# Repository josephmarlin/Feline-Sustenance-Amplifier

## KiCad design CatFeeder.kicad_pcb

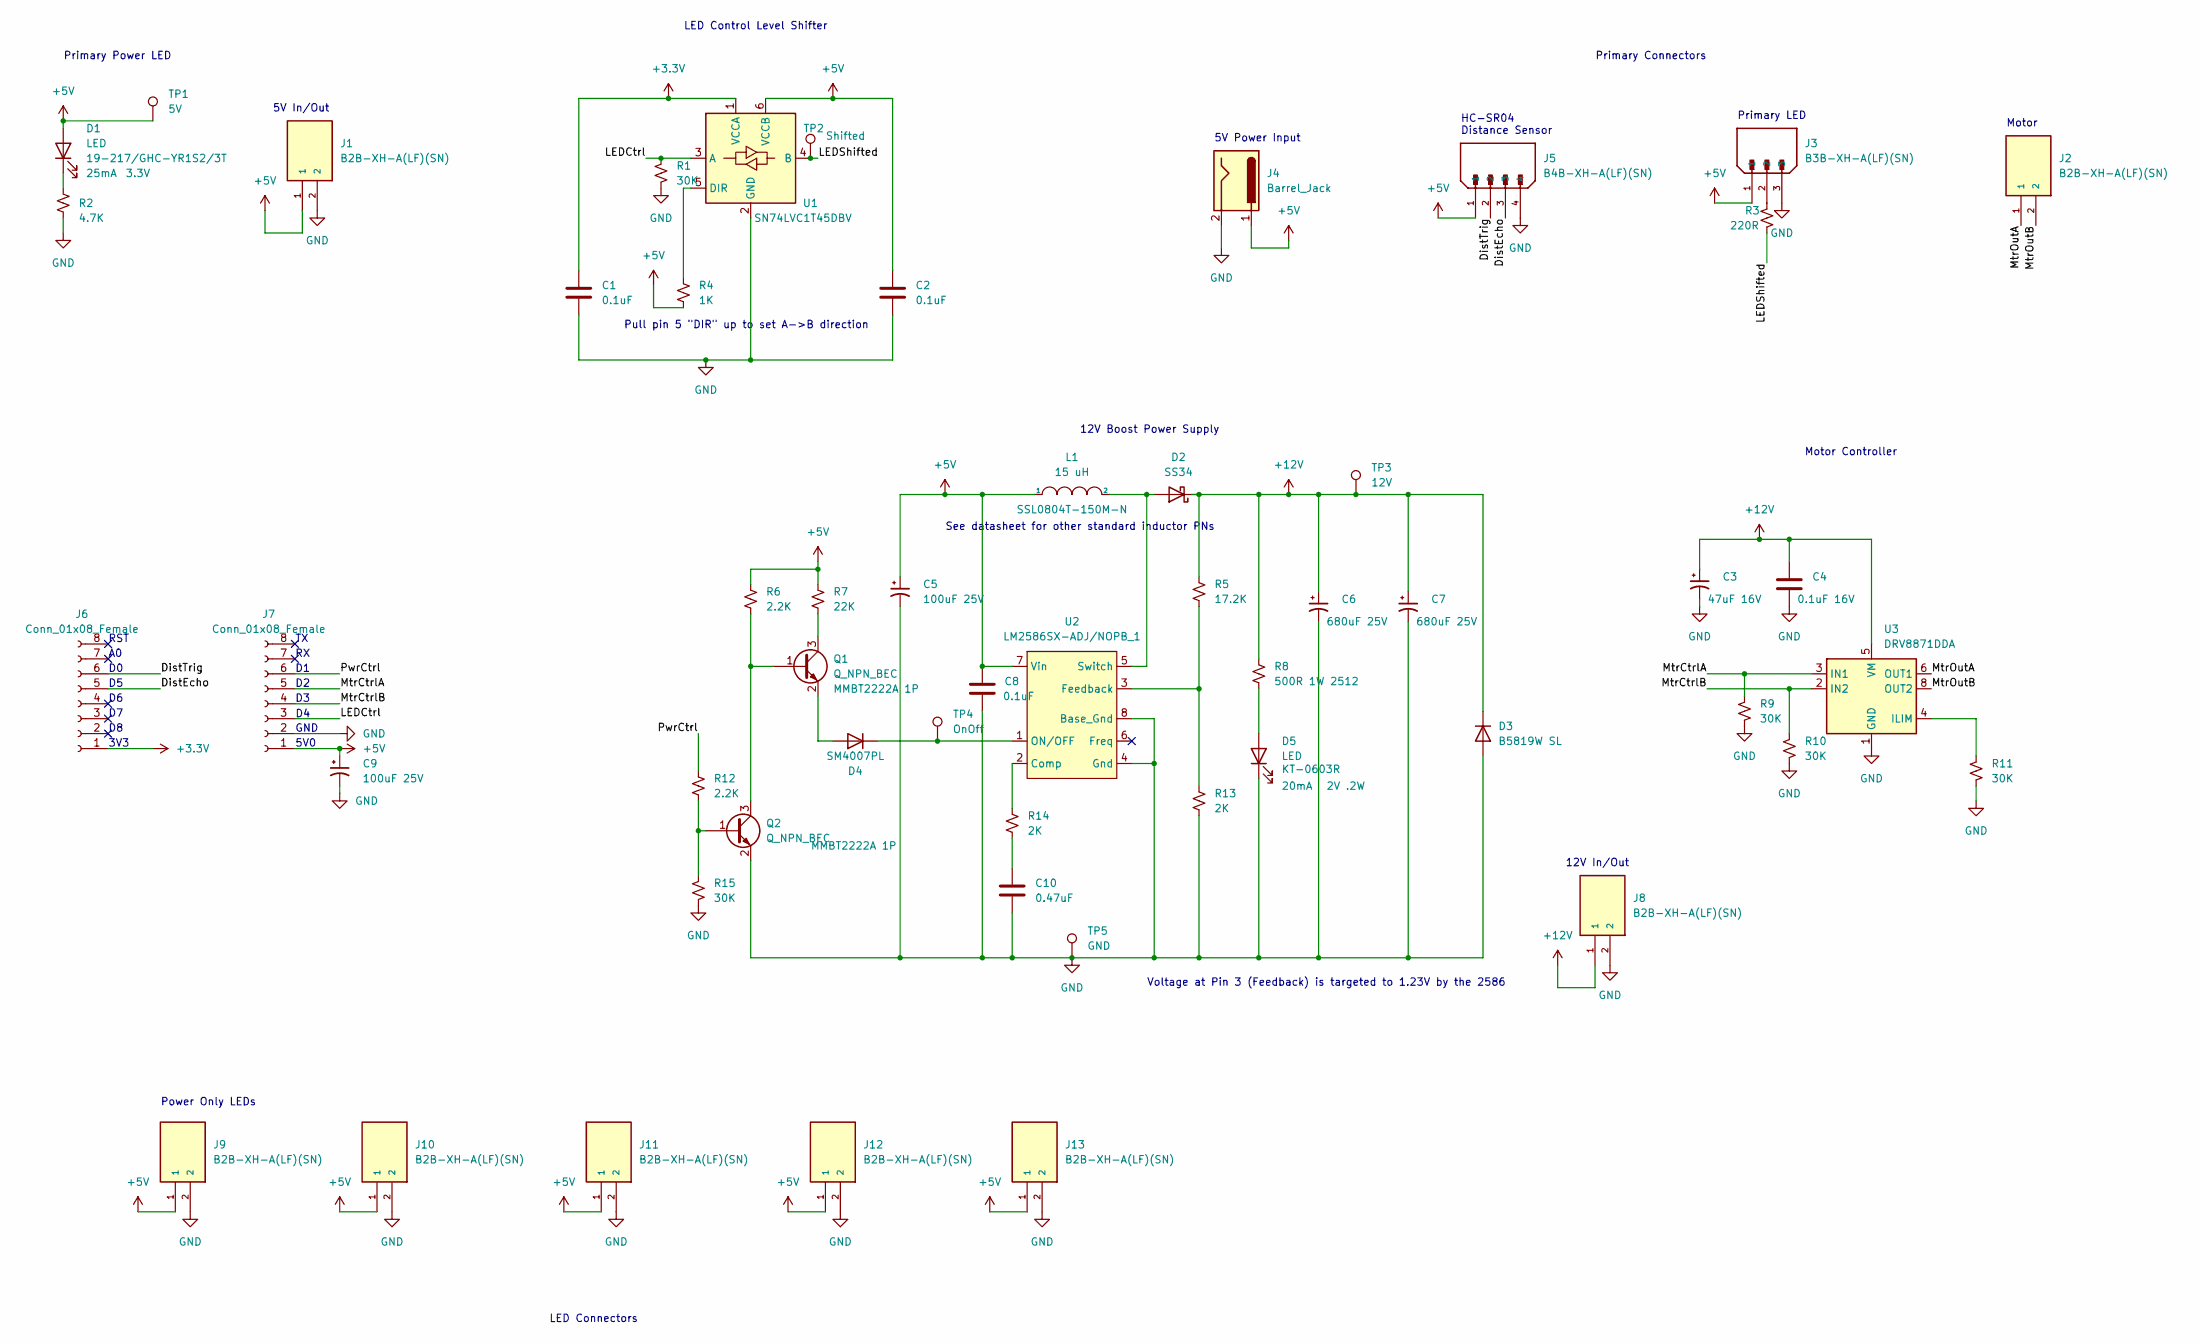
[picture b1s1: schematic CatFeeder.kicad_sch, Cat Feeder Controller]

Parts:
C1, C2, C8: 0.1uF; C_0402_1005Metric
C3: 47uF 16V; CP_Elec_5x5.4
C4: 0.1uF 16V; C_0402_1005Metric
C5, C9: 100uF 25V; CP_Radial_D8.0mm_P3.50mm
C6, C7: 680uF 25V; CP_Radial_D8.0mm_P3.50mm
C10: 0.47uF; C_0603_1608Metric
D1: LED; LED_0603_1608Metric; Voltage 3.3V
D2: SS34; D_SMA
D3: B5819W SL; D_SOD-123
D4: SM4007PL; D_SOD-123F
D5: LED; LED_0603_1608Metric; Voltage 2V .2W
J1, J2, J8, J9, J10, J11, J12, J13: B2B-XH-A(LF)(SN); JST_XH_B2B-XH-A_1x02_P2.50mm_Vertical
J3: B3B-XH-A(LF)(SN); JST_XH_B3B-XH-A_1x03_P2.50mm_Vertical; PARTREV N/A
J4: Barrel_Jack; BarrelJack_CUI_PJ-063AH_Horizontal
J5: B4B-XH-A(LF)(SN); JST_XH_B4B-XH-A_1x04_P2.50mm_Vertical; PARTREV N/A
J6, J7: Conn_01x08_Female; PinSocket_1x08_P2.54mm_Vertical
L1: 15 uH; SSL0804_Inductor_SMD
Q1, Q2: Q_NPN_BEC; SOT-23
R1, R9, R10, R11, R15: 30K; R_0402_1005Metric
R2: 4.7K; R_0805_2012Metric
R3: 220R; R_0805_2012Metric
R4: 1K; R_0402_1005Metric
R5: 17.2K; R_0603_1608Metric
R6, R12: 2.2K; R_0805_2012Metric
R7: 22K; R_0805_2012Metric
R8: 500R 1W 2512; R_2512_6332Metric
R13, R14: 2K; R_0402_1005Metric
TP1: 5V; TestPoint_Pad_D1.5mm
TP2: Shifted; TestPoint_Pad_D1.5mm
TP3: 12V; TestPoint_Pad_D1.5mm
TP4: OnOff; TestPoint_Pad_D1.0mm
TP5: GND; TestPoint_Pad_D1.5mm
U1: SN74LVC1T45DBV; SOT-23-6
U2: LM2586SX-ADJ/NOPB_1; TO-263-7_TabPin8
U3: DRV8871DDA; Texas_HTSOP-8-1EP_3.9x4.9mm_P1.27mm_EP2.95x4.9mm_Mask2.4x3.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

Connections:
+3.3V: C1.1, J6.1, U1.1 (VCCA)
+5V: C2.1, C5.1, C8.1, C9.1, D1.2 (A), J1.1, J3.1, J4.1, J5.1, J7.1, J9.1, J10.1, J11.1, J12.1, J13.1, L1.1, R4.2, R6.1, R7.1, TP1.1, U1.6 (VCCB), U2.7 (Vin)
+12V: C3.1, C4.1, C6.1, C7.1, D2.1 (K), D3.2 (K), J8.1, R5.1, R8.1, TP3.1, U3.5 (VM)
/DistEcho: J5.3, J6.5
/DistTrig: J5.2, J6.6
/LEDCtrl: J7.3, R1.1, U1.3 (A)
/LEDShifted: R3.2, TP2.1, U1.4 (B)
/MtrCtrlA: J7.5, R9.1, U3.3 (IN1)
/MtrCtrlB: J7.4, R10.1, U3.2 (IN2)
/MtrOutA: J2.1, U3.6 (OUT1)
/MtrOutB: J2.2, U3.8 (OUT2)
/PwrCtrl: J7.6, R12.1
GND: C1.2, C2.2, C3.2, C4.2, C5.2, C6.2, C7.2, C8.2, C9.2, C10.2, D3.1 (A), D5.1 (K), J1.2, J3.3, J4.2, J5.4, J7.2, J8.2, J9.2, J10.2, J11.2, J12.2, J13.2, Q2.2 (E), R1.2, R2.2, R9.2, R10.2, R11.2, R13.2, R15.2, TP5.1, U1.2 (GND), U2.4 (Gnd), U2.8 (Base_Gnd), U3.1 (GND), U3.7 (GND), U3.9 (GND)
unnamed: C10.1, R14.2
unnamed: D1.1 (K), R2.1
unnamed: D2.2 (A), L1.2, U2.5 (Switch)
unnamed: D4.1 (K), TP4.1, U2.1 (ON/OFF)
unnamed: D4.2 (A), Q1.2 (E)
unnamed: D5.2 (A), R8.2
unnamed: J3.2, R3.1
unnamed: Q1.1 (B), Q2.3 (C), R6.2
unnamed: Q1.3 (C), R7.2
unnamed: Q2.1 (B), R12.2, R15.1
unnamed: R4.1, U1.5 (DIR)
unnamed: R11.1, U3.4 (ILIM)
unnamed: R5.2, R13.1, U2.3 (Feedback)
unnamed: R14.1, U2.2 (Comp)

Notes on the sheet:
HC-SR04 Distance Sensor
5V0
Voltage at Pin 3 (Feedback) is targeted to 1.23V by the 2586
Motor
Primary LED
Power Only LEDs
Primary Power LED
Motor Controller
5V In/Out
5V Power Input
RST
LED Control Level Shifter
Pull pin 5 "DIR" up to set A->B direction
Primary Connectors
12V Boost Power Supply
12V In/Out
3V3
GND
LED Connectors
See datasheet for other standard inductor PNs

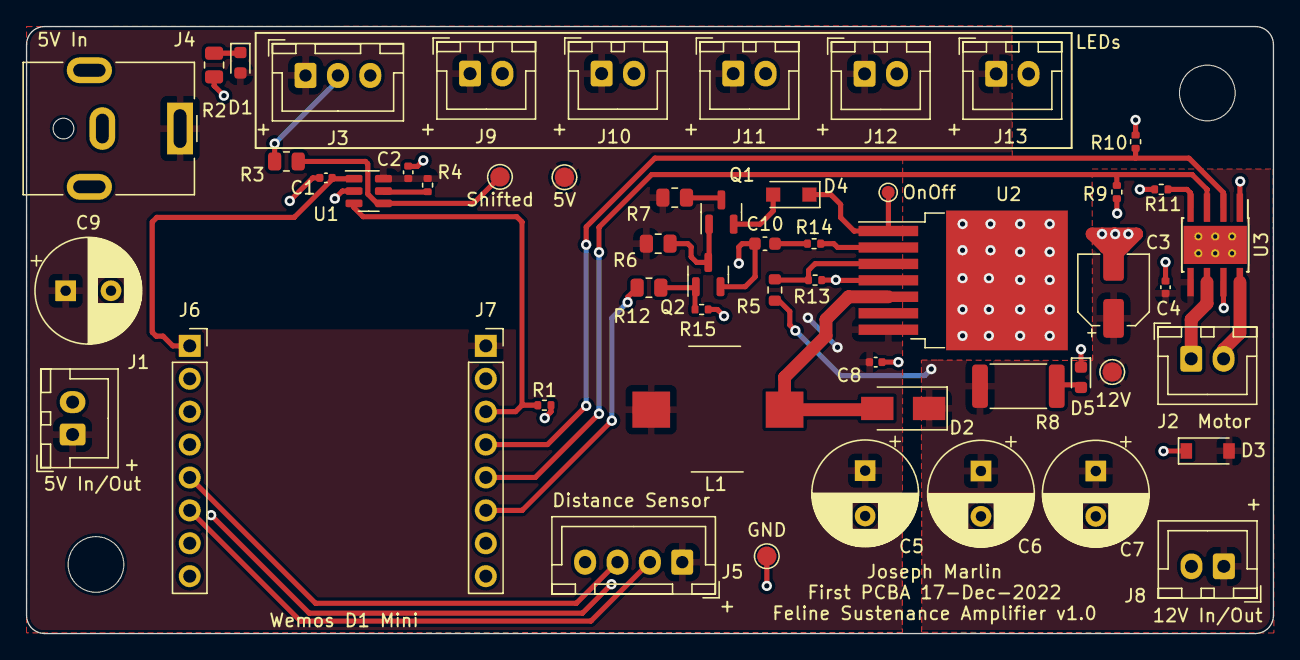
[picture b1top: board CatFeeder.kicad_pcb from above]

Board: 2 copper layers, 96.3 x 46.9 mm, 54 parts (0 on the bottom side), 27 nets.

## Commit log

2022-12-05 ignore the auto-save file
2022-12-13 Added power plane to top layer, fixed some layout errors
2022-12-14 Add pull ups to signals, tweak layout, reduce board size, add mounting holes
2022-12-19 added series resistor for neopixel control line, layout improvements, changed suspect resistors to 0805 for easier future rework
2022-12-19 rounded corners, added polarity silkscreen, dimmed the main power LED, fixed polarized cap schematic symbols.
2022-12-23 Manufacturing outputs
2023-03-10 final revision, as fabricated
2023-03-10 Add basic driver code
